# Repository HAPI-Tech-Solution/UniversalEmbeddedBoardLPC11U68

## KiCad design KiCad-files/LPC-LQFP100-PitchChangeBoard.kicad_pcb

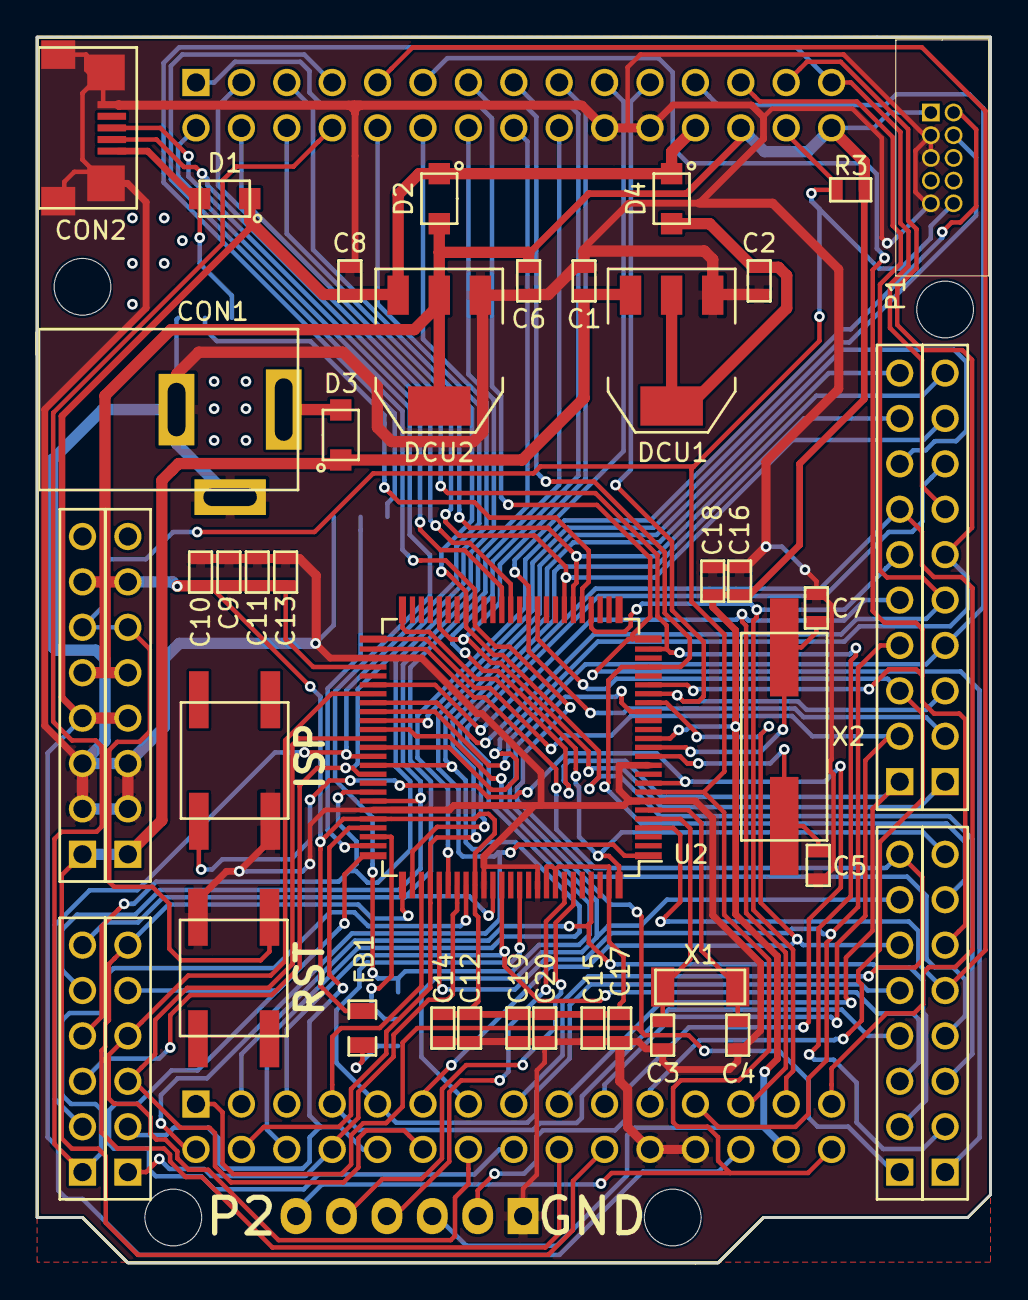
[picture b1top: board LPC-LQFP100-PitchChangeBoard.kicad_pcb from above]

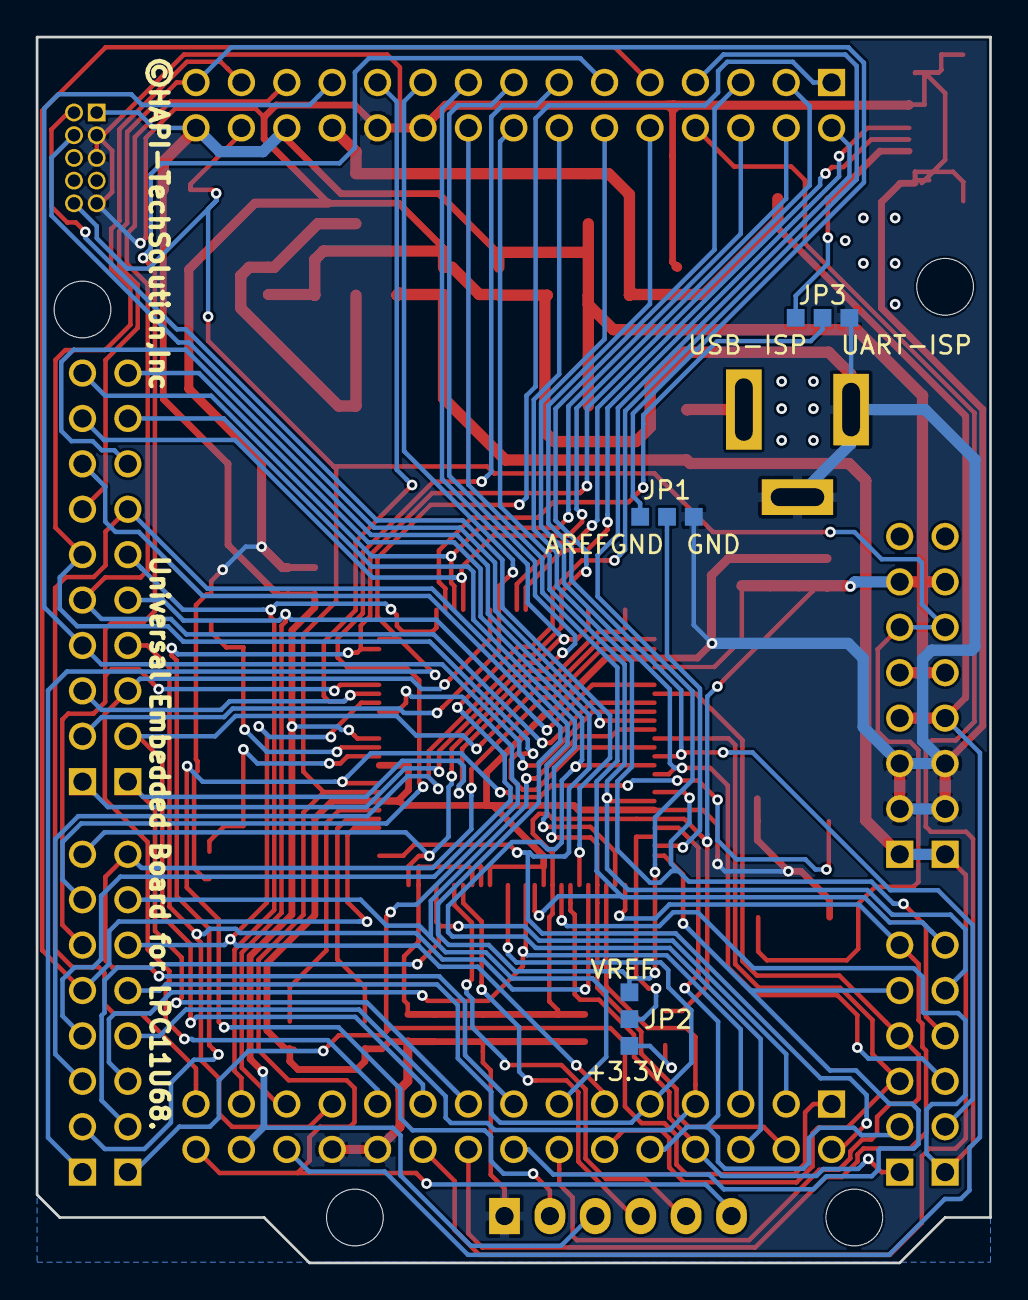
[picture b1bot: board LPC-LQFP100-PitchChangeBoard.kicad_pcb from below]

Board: 2 copper layers, 53.3 x 68.6 mm, 42 parts (5 on the bottom side), 71 nets.

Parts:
C1, C2, C6, C8, C17: 1uF; SMD-0603
C3, C4: 18pF; SMD-0603
C5, C7: 27pF; SMD-0603
C9, C11, C12, C15, C18, C19: 0.1uF; SMD-0603
C10, C13, C14, C16, C20: 0.01uF; SMD-0603
CON1: MJ-179P; DCJack_MJ-179P
CON2: HIROSE ZX62R-B-5P; Hirose-microUSB-ZX62R-B-5P
D1, D2, D3, D4: PMEG2010ER,115
DCU1: AZ1117E-5.0V; SOT-223
DCU2: AZ1117E-3.3V; SOT-223
FB1: R; SMD-0805
JP1, JP2, JP3: JUMPER3; SJ-3Pin
OPT1: Arduino-Shiled2(11x)Inside; Arduino-Shield-Inside-Outline
OPT2: Arduino-Shiled; Arduino-Shield-Normal-Outline
P1: CONN_02X05; JTAG-Half-2x5
P2: CONN_01X06; Pin_Header_Angled_1x06
R3: 100k; SMD-0603
SW1, SW2: SW_PUSH; SW_TACT-EVQQ2Y03W
U2: LPC11U68JBD100; LPC11E68-TQFP-100
X1: 32.768KHZ; FC-255-RTC-Xtal
X2: 12MHz; HC-49_S

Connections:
+3V3: C6.1, C9.1, C10.1, C11.1, C12.1, C13.1, C14.1, C15.1, C16.1, C17.1, C18.2, C19.1, C20.1, D2.1, DCU2.2, DCU2.4, FB1.1, OPT1.28, OPT1.30, OPT2.28, OPT2.30, P1.1, P2.3, R3.2, U2.14, U2.54, U2.71, U2.84, U2.92, U2.93, U2.99
+5V: C8.1, D1.2, D2.2, D4.2, DCU2.3, OPT1.27, OPT2.27
AREFGND: JP1.3, OPT2.14
GND: C1.1, C2.1, C3.2, C4.1, C5.2, C6.2, C7.1, C8.2, C9.2, C10.2, C11.2, C12.2, C13.2, C14.2, C15.2, C16.2, C17.2, C18.1, C19.2, C20.2, CON1.2, CON1.3, CON2.5, CON2.6, CON2.7, CON2.8, CON2.9, DCU1.1, DCU2.1, JP1.1, JP3.3, OPT1.25, OPT1.26, OPT2.25, OPT2.26, P1.3, P1.5, P1.9, P2.1, SW1.2, SW2.2, U2.7, U2.11, U2.53, U2.70, U2.85, U2.91
ISP: P2.2, SW2.1, U2.9
unnamed: C2.2, D4.1, DCU1.2, DCU1.4
unnamed: C3.1, U2.5, X1.1
unnamed: C4.2, U2.6, X1.2
unnamed: C5.1, U2.12, X2.1
unnamed: C7.2, U2.13, X2.2
unnamed: CON1.1, D3.1
unnamed: FB1.2, JP2.1
unnamed: JP1.2, U2.74
unnamed: JP2.2, U2.73
PIO0_2: OPT2.10, U2.19
PIO0_3(USB_VBUS): JP3.2, U2.30
PIO0_4: OPT2.17, U2.31
PIO0_5: OPT2.16, U2.32
PIO0_8: OPT2.12, U2.58
PIO0_9: OPT2.11, U2.59
PIO0_11: OPT2.19, U2.64
PIO0_12: OPT2.20, U2.66
PIO0_13: OPT2.21, U2.68
PIO0_14: OPT2.22, U2.69
PIO0_16: OPT1.18, U2.82
PIO0_18: P2.4, U2.94
PIO0_19: P2.5, U2.95
PIO0_20: OPT1.0, U2.17
PIO0_22: OPT1.20, U2.62
PIO0_23: OPT2.18, U2.83
PIO1_0: OPT1.1, U2.97
PIO1_3: OPT1.19, U2.72
PIO1_8: OPT1.6, U2.61
PIO1_9: OPT2.23, U2.86
PIO1_10: OPT1.5, U2.18
PIO1_11: OPT1.17, U2.65
PIO1_12: OPT1.4, U2.89
PIO1_13: OPT1.3, U2.78
PIO1_14: OPT1.16, U2.79
PIO1_15: OPT1.2, U2.87
PIO1_18: OPT2.2, U2.43
PIO1_19: OPT2.4, U2.4
PIO1_20: OPT1.13, U2.29
PIO1_21: OPT1.12, U2.56
PIO1_22: OPT1.11, U2.80
PIO1_23: OPT1.10, U2.35
PIO1_24: OPT2.3, U2.42
PIO1_25: OPT2.7, U2.100
PIO1_26: OPT2.5, U2.20
PIO1_27: OPT2.6, U2.22
PIO1_28: OPT2.8, U2.46
PIO1_29: OPT2.13, U2.63
PIO2_3: OPT2.9, U2.36
PIO2_11: OPT2.0, U2.25
PIO2_12: OPT2.1, U2.24
PIO2_16: OPT1.8, U2.50
PIO2_17: OPT1.9, U2.51
PIO2_18: OPT1.7, U2.52
PIO2_19: OPT1.21, U2.57
PIO2_20: OPT1.22, U2.75
PIO2_21: OPT1.23, U2.76
PIO2_22: OPT1.14, U2.77
PIO2_23: OPT1.15, U2.1
RESETn: OPT1.29, OPT2.29, P1.10, P2.6, R3.1, SW1.1, U2.8
SWCLK: P1.4, U2.60
SWDIO: P1.2, U2.81
USB-VDD: CON2.1, D1.1, JP3.1
USB_DM: CON2.2, U2.38
USB_DP: CON2.3, U2.39
VREF: JP2.3, OPT2.15
Vin: C1.2, D3.2, DCU1.3, OPT1.24, OPT2.24

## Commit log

2015-05-29 FirstCommit,orgin
2015-05-29 no message

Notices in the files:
KiCad-files/LPC-LQFP100-PitchChangeBoard.kicad_pcb:
©HAPI-TechSolution,Inc
